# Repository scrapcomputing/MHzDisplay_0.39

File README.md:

# A Turbo LED MHz Display with 0.39" sized digits

A MHz Turbo LED display with 2x smaller 0.39" digits (12.8mm x 9.7mm x 7.0mm common cathode like the HD1107G).
These are smaller than the more common 0.56" display like the [TD-37S](https://github.com/scrapcomputing/MHzDisplayBlaster) or the [K568](https://github.com/scrapcomputing/MHzDisplay_K568).

I don't know the model number of the display that this is compatible with. If you do know please let me know!

As all similar displays, it is powered by 5V DC (pins +5V, G) and it can display a Turbo and a non-Turbo number, depending on the state of the Turbo switch (pins L C H, Low Common High).
It also drives the Turbo LED accordingly (pins T- and T+).

My case did not have an LED display that I could clone, so this is a design based on other common displays, like the [TD-37S](https://github.com/scrapcomputing/MHzDisplayBlaster).

Because of the limited space between the mounting holes, I had to the split the segment selection headers into two parts. The smaller headers are for segment G and the dot (DP).

# BOM

Gerber files are published in the [releases](https://github.com/scrapcomputing/MHzDisplay_0.39/releases).

Quantity | Item
---------|-------------------------------
2        | 2x13 2.54mm pitch pin headers
2        | 2x3  2.54mm pitch pin headers
1        | 1x7  2.54mm pitch pin header
1        | 100 Ohm 1/4 watt resistor (or smaller value for brighter display)
2        | Single-digit 7-segment Common-Cathode 0.39" displays that fit the PCB (display dimensions 9.7mm x 12.8mm x 7.0mm), like the HD1107G.
1        | [PCB](https://github.com/scrapcomputing/MHzDisplay_0.39/releases)

# Schematic

# Photos

# Resources about MHz displays

- The best resource for MHz displays: [minuszerodegrees.net](https://www.minuszerodegrees.net/led_speed_display/led_speed_display.htm). It includes photos and manuals for a large selection of displays.

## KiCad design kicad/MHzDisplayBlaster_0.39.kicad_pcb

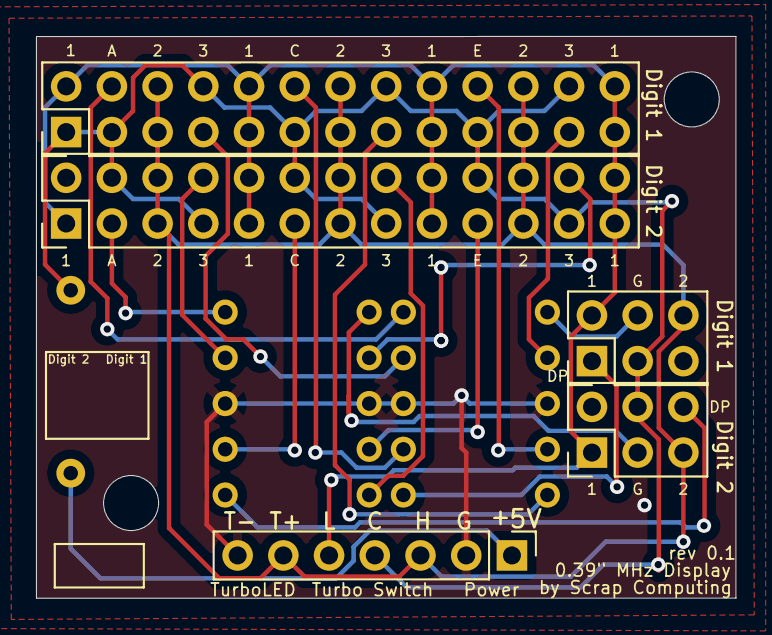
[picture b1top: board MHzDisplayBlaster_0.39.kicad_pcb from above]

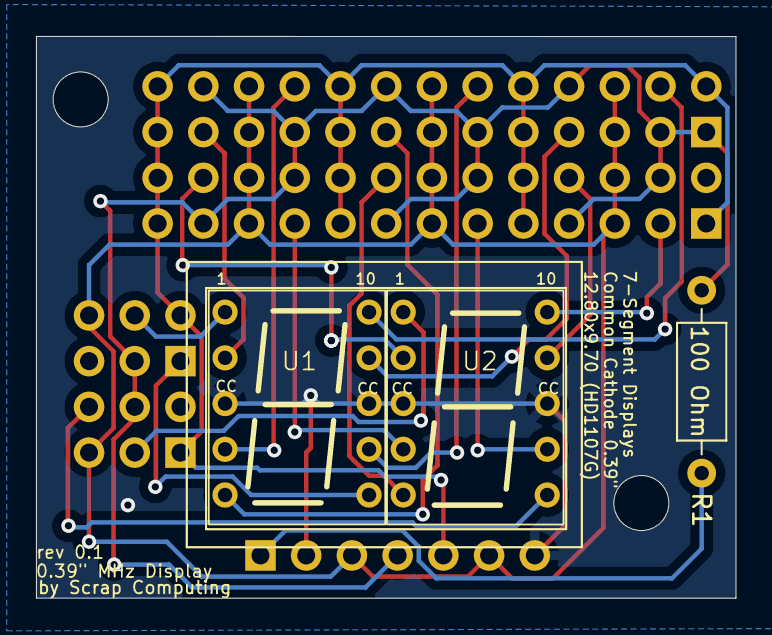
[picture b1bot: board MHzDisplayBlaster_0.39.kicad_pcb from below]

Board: 2 copper layers, 38.9 x 31.2 mm, 8 parts (3 on the bottom side), 21 nets.

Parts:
J1: Conn_02x13 DigitRHS; PinHeader_2x13_P2.54mm_Vertical
J2: Conn_02x14 DigitLHS; PinHeader_2x13_P2.54mm_Vertical
J3, J5: Conn_02x03_Odd_Even; PinHeader_2x03_P2.54mm_Vertical
J4: Conn_01x07; PinHeader_1x07_P2.54mm_Vertical
R1: 100 Ohm; R_Axial_DIN0207_L6.3mm_D2.5mm_P10.16mm_Horizontal
U1, U2: SC39-11GWA; HD1107

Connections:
1: J1.1, J1.9, J1.10, J1.17, J1.18, J1.25, J1.26, J2.2, J2.9, J2.10, J2.17, J2.18, J2.25, J2.26, J3.2, J4.5, J5.1
2: J1.5, J1.6, J1.13, J1.14, J1.21, J1.22, J2.5, J2.6, J2.13, J2.14, J2.21, J2.22, J3.6, J4.3, J4.6, J5.5
3: J1.4, J1.7, J1.12, J1.15, J1.20, J1.23, J2.1, J2.3, J2.8, J2.11, J2.16, J2.19, J2.24, J3.3, J4.4, J5.4, R1.1
+5V: J4.1, R1.2
DIG1_A: J2.4, U1.10 (A)
DIG1_B: J2.7, U1.9 (B)
DIG1_C: J2.12, U1.7 (C)
DIG1_CC: J4.2, J4.7, U1.3 (CC), U1.8 (CC), U2.3 (CC), U2.8 (CC)
DIG1_D: J2.15, U1.5 (D)
DIG1_DP: J3.1, U1.6 (DP)
DIG1_E: J2.20, U1.4 (E)
DIG1_F: J2.23, U1.2 (F)
DIG1_G: J3.4, U1.1 (G)
DIG2_A: J1.3, U2.10 (A)
DIG2_B: J1.8, U2.9 (B)
DIG2_C: J1.11, U2.7 (C)
DIG2_D: J1.16, U2.5 (D)
DIG2_DP: J5.6, U2.6 (DP)
DIG2_E: J1.19, U2.4 (E)
DIG2_F: J1.24, U2.2 (F)
DIG2_G: J5.3, U2.1 (G)

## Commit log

2025-07-27 Rev 0.1
